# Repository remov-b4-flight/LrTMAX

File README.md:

# LrTMAX
Adobe Lightroom MIDI Developer Controller project (STM32F072Cx based)  
LrTMAX MIDI controller is formed by embedded hardware circuit board and its firmware.  
It used with [MIDI2LR](https://github.com/rsjaffe/MIDI2LR) software,  
You can control development parameters on RAW/JPEG photos.  
## Video(in brother project LrE-6)
  
detailed Video on [YouTube (LrE-6)](https://www.youtube.com/watch?v=oeDpP1sG9_Y)  
## Photo
  
LrTMAX is near to [LrE-6](https://github.com/remov-b4-flight/LrE-6)  
Information related Build,Configure & Use are exists on wiki.  
***
"Lightroom Classic" is Registerd Trademark of Adobe Corporation.

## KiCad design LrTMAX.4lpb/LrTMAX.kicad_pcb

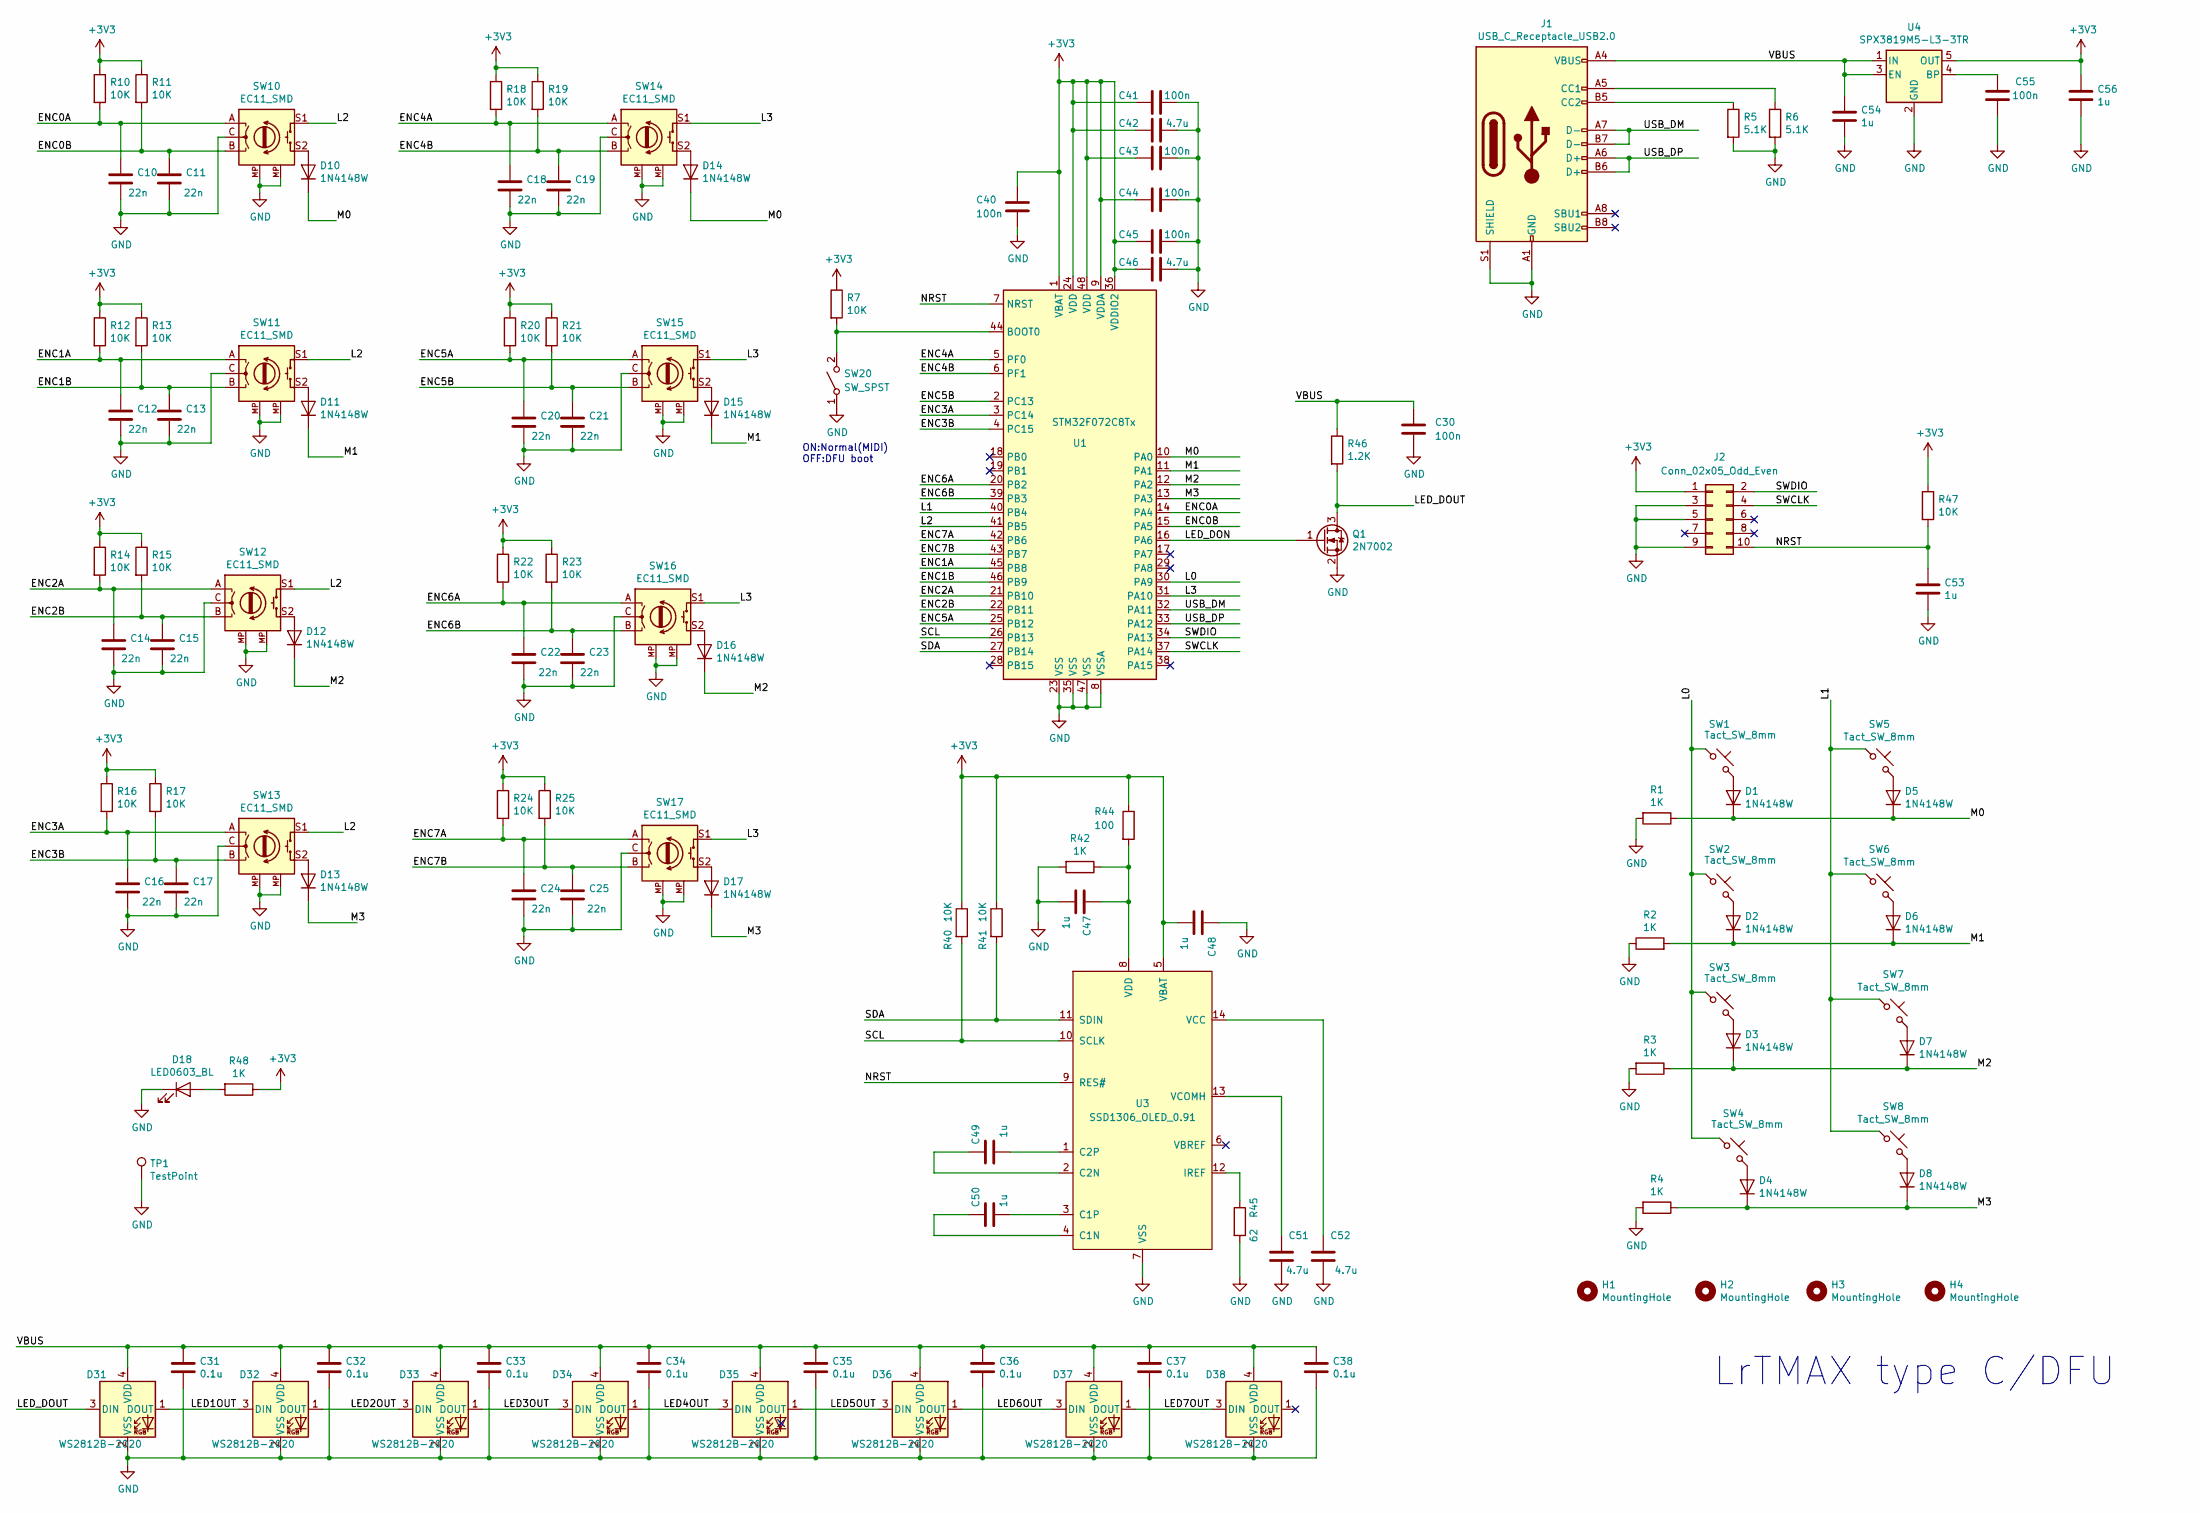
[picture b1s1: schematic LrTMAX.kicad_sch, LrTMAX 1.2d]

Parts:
C10, C11, C12, C13, C14, C15, C16, C17, C18, C19, C20, C21, C22, C23, C24, C25: 22n; C_0805_2012Metric
C30, C55: 100n; C_0805_2012Metric
C31, C32, C33, C34, C35, C36, C37, C38: 0.1u; C_0805_2012Metric
C40, C41, C43, C44, C45: 100n; C_0603_1608Metric
C42, C46, C51, C52: 4.7u; C_0805_2012Metric
C47, C48, C49, C50, C53, C54, C56: 1u; C_0805_2012Metric
D1, D2, D3, D4, D5, D6, D7, D8, D10, D11, D12, D13, D14, D15, D16, D17: 1N4148W; D_SOD-123
D18: LED0603_BL; LED_0603_1608Metric
D31, D32, D33, D34, D35, D36, D37, D38: WS2812B-2020; LED_WS2812B-2020
H1, H2, H3, H4: MountingHole; MountingHole_2.7mm_M2.5
J1: USB_C_Receptacle_USB2.0; USB_C_Receptacle_HRO_TYPE-C-31-M-12
J2: Conn_02x05_Odd_Even; PinHeader_2x05_P1.27mm_Vertical
Q1: 2N7002; SOT-23
R1, R2, R3, R4, R42, R48: 1K; R_0805_2012Metric
R5, R6: 5.1K; R_0805_2012Metric
R7, R10, R11, R12, R13, R14, R15, R16, R17, R18, R19, R20, R21, R22, R23, R24, R25, R40, R41, R47: 10K; R_0805_2012Metric
R44: 100; R_0805_2012Metric
R45: 62; R_0805_2012Metric
R46: 1.2K; R_0805_2012Metric
SW1, SW2, SW3, SW4, SW5, SW6, SW7, SW8: Tact_SW_8mm; SW_PUSH_6mm_H9.5mm
SW10, SW11, SW12, SW13, SW14, SW15, SW16, SW17: EC11_SMD; RotaryEncoder_Alps_EC11E-Switch_Vertical_H20mm
SW20: SW_SPST; SW_DIP_SPSTx01_Slide_Copal_CHS-01B_W7.62mm_P1.27mm
TP1: TestPoint; TestPoint_THTPad_D1.0mm_Drill0.5mm
U1: STM32F072C8Tx; LQFP-48_7x7mm_P0.5mm
U3: SSD1306_OLED_0.91; OLED-9.1
U4: SPX3819M5-L3-3TR; SOT-23-5

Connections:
+3V3: C40.1, C41.2, C42.2, C43.2, C44.2, C45.2, C46.2, C48.1, C56.1, J2.1, R7.1, R10.1, R11.1, R12.1, R13.1, R14.1, R15.1, R16.1, R17.1, R18.1, R19.1, R20.1, R21.1, R22.1, R23.1, R24.1, R25.1, R40.1, R41.1, R44.1, R47.1, R48.1, U1.1 (VBAT), U1.9 (VDDA), U1.24 (VDD), U1.36 (VDDIO2), U1.48 (VDD), U3.5 (VBAT), U4.5 (OUT)
/ENC0A: C10.1, R10.2, SW10.A, U1.14 (PA4)
/ENC0B: C11.1, R11.2, SW10.B, U1.15 (PA5)
/ENC1A: C12.1, R12.2, SW11.A, U1.45 (PB8)
/ENC1B: C13.1, R13.2, SW11.B, U1.46 (PB9)
/ENC2A: C14.1, R14.2, SW12.A, U1.21 (PB10)
/ENC2B: C15.1, R15.2, SW12.B, U1.22 (PB11)
/ENC3A: C16.1, R16.2, SW13.A, U1.3 (PC14)
/ENC3B: C17.1, R17.2, SW13.B, U1.4 (PC15)
/ENC4A: C18.1, R18.2, SW14.A, U1.5 (PF0)
/ENC4B: C19.1, R19.2, SW14.B, U1.6 (PF1)
/ENC5A: C20.1, R20.2, SW15.A, U1.25 (PB12)
/ENC5B: C21.1, R21.2, SW15.B, U1.2 (PC13)
/ENC6A: C22.1, R22.2, SW16.A, U1.20 (PB2)
/ENC6B: C23.1, R23.2, SW16.B, U1.39 (PB3)
/ENC7A: C24.1, R24.2, SW17.A, U1.42 (PB6)
/ENC7B: C25.1, R25.2, SW17.B, U1.43 (PB7)
/L0: SW1.1, SW2.1, SW3.1, SW4.1, U1.30 (PA9)
/L1: SW5.1, SW6.1, SW7.1, SW8.1, U1.40 (PB4)
/L2: SW10.S1, SW11.S1, SW12.S1, SW13.S1, U1.41 (PB5)
/L3: SW14.S1, SW15.S1, SW16.S1, SW17.S1, U1.31 (PA10)
/LED1OUT: D31.1 (DOUT), D32.3 (DIN)
/LED2OUT: D32.1 (DOUT), D33.3 (DIN)
/LED3OUT: D33.1 (DOUT), D34.3 (DIN)
/LED4OUT: D34.1 (DOUT), D35.3 (DIN)
/LED5OUT: D35.1 (DOUT), D36.3 (DIN)
/LED6OUT: D36.1 (DOUT), D37.3 (DIN)
/LED7OUT: D37.1 (DOUT), D38.3 (DIN)
/LED_DON: Q1.1 (G), U1.16 (PA6)
/LED_DOUT: D31.3 (DIN), Q1.3 (D), R46.2
/M0: D1.1 (K), D5.1 (K), D10.1 (K), D14.1 (K), R1.1, U1.10 (PA0)
/M1: D2.1 (K), D6.1 (K), D11.1 (K), D15.1 (K), R2.2, U1.11 (PA1)
/M2: D3.1 (K), D7.1 (K), D12.1 (K), D16.1 (K), R3.1, U1.12 (PA2)
/M3: D4.1 (K), D8.1 (K), D13.1 (K), D17.1 (K), R4.1, U1.13 (PA3)
/NRST: C53.1, J2.10, R47.2, U1.7 (NRST), U3.9 (RES#)
/SCL: R40.2, U1.26 (PB13), U3.10 (SCLK)
/SDA: R41.2, U1.27 (PB14), U3.11 (SDIN)
/SWCLK: J2.4, U1.37 (PA14)
/SWDIO: J2.2, U1.34 (PA13)
/USB_DM: J1.A7 (D-), J1.B7 (D-), U1.32 (PA11)
/USB_DP: J1.A6 (D+), J1.B6 (D+), U1.33 (PA12)
/VBUS: C30.1, C31.1, C32.1, C33.1, C34.1, C35.1, C36.1, C37.1, C38.1, C54.1, D31.4 (VDD), D32.4 (VDD), D33.4 (VDD), D34.4 (VDD), D35.4 (VDD), D36.4 (VDD), D37.4 (VDD), D38.4 (VDD), J1.A4 (VBUS), J1.A9 (VBUS), J1.B4 (VBUS), J1.B9 (VBUS), R46.1, U4.1 (IN), U4.3 (EN)
GND: C10.2, C11.2, C12.2, C13.2, C14.2, C15.2, C16.2, C17.2, C18.2, C19.2, C20.2, C21.2, C22.2, C23.2, C24.2, C25.2, C30.2, C31.2, C32.2, C33.2, C34.2, C35.2, C36.2, C37.2, C38.2, C40.2, C41.1, C42.1, C43.1, C44.1, C45.1, C46.1, C47.1, C48.2, C51.1, C52.1, C53.2, C54.2, C55.2, C56.2, D18.1 (K), D31.2 (VSS), D32.2 (VSS), D33.2 (VSS), D34.2 (VSS), D35.2 (VSS), D36.2 (VSS), D37.2 (VSS), D38.2 (VSS), J1.A1 (GND), J1.A12 (GND), J1.B1 (GND), J1.B12 (GND), J1.S1 (SHIELD), J2.3, J2.5, J2.9, Q1.2 (S), R1.2, R2.1, R3.2, R4.2, R5.2, R6.2, R42.2, R45.2, SW10.C, SW10.MP (GND), SW11.C, SW11.MP (GND), SW12.C, SW12.MP (GND), SW13.C, SW13.MP (GND), SW14.C, SW14.MP (GND), SW15.C, SW15.MP (GND), SW16.C, SW16.MP (GND), SW17.C, SW17.MP (GND), SW20.1 (A), TP1.1, U1.8 (VSSA), U1.23 (VSS), U1.35 (VSS), U1.47 (VSS), U3.7 (VSS), U4.2 (GND)
unnamed: C47.2, R42.1, R44.2, U3.8 (VDD)
unnamed: C49.1, U3.2 (C2N)
unnamed: C49.2, U3.1 (C2P)
unnamed: C50.1, U3.4 (C1N)
unnamed: C50.2, U3.3 (C1P)
unnamed: C51.2, U3.13 (VCOMH)
unnamed: C52.2, U3.14 (VCC)
unnamed: C55.1, U4.4 (BP)
unnamed: D1.2 (A), SW1.2
unnamed: D2.2 (A), SW2.2
unnamed: D3.2 (A), SW3.2
unnamed: D4.2 (A), SW4.2
unnamed: D5.2 (A), SW5.2
unnamed: D6.2 (A), SW6.2
unnamed: D7.2 (A), SW7.2
unnamed: D8.2 (A), SW8.2
unnamed: D10.2 (A), SW10.S2
unnamed: D11.2 (A), SW11.S2
unnamed: D12.2 (A), SW12.S2
unnamed: D13.2 (A), SW13.S2
unnamed: D14.2 (A), SW14.S2
unnamed: D15.2 (A), SW15.S2
unnamed: D16.2 (A), SW16.S2
unnamed: D17.2 (A), SW17.S2
unnamed: D18.2 (A), R48.2
unnamed: J1.A5 (CC1), R6.1
unnamed: J1.B5 (CC2), R5.1
unnamed: R7.2, SW20.2 (B), U1.44 (BOOT0)
unnamed: R45.1, U3.12 (IREF)

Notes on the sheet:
LrTMAX type C/DFU
ON:Normal(MIDI) OFF:DFU boot

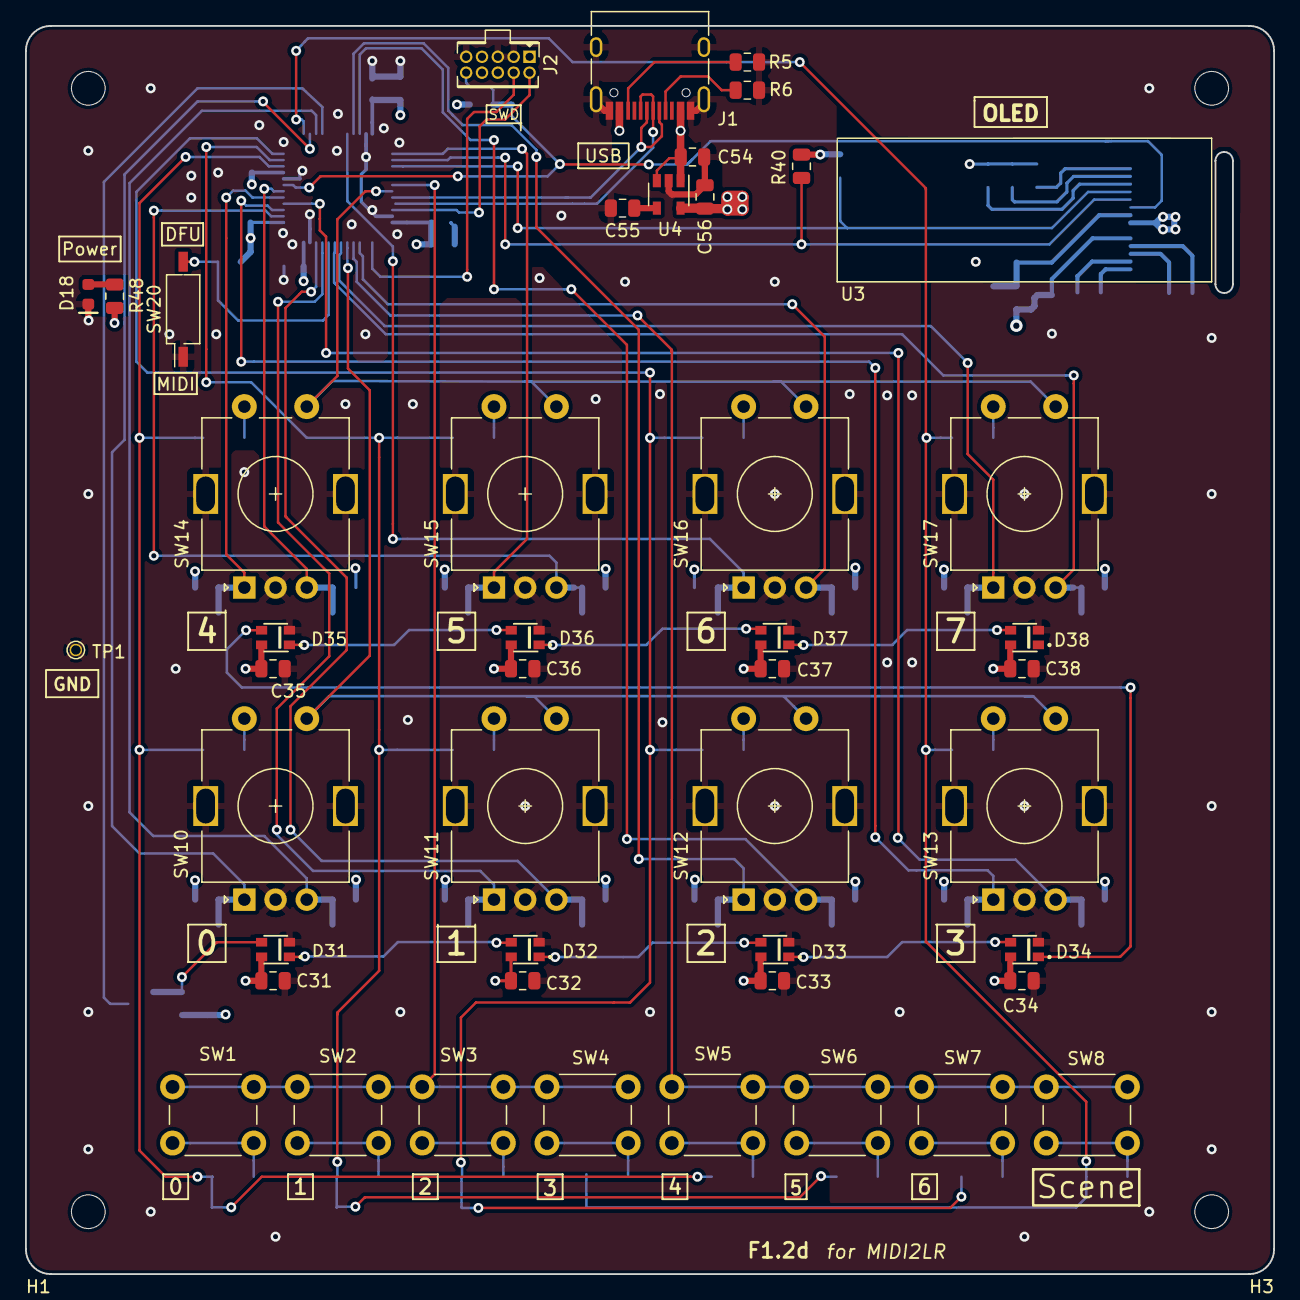
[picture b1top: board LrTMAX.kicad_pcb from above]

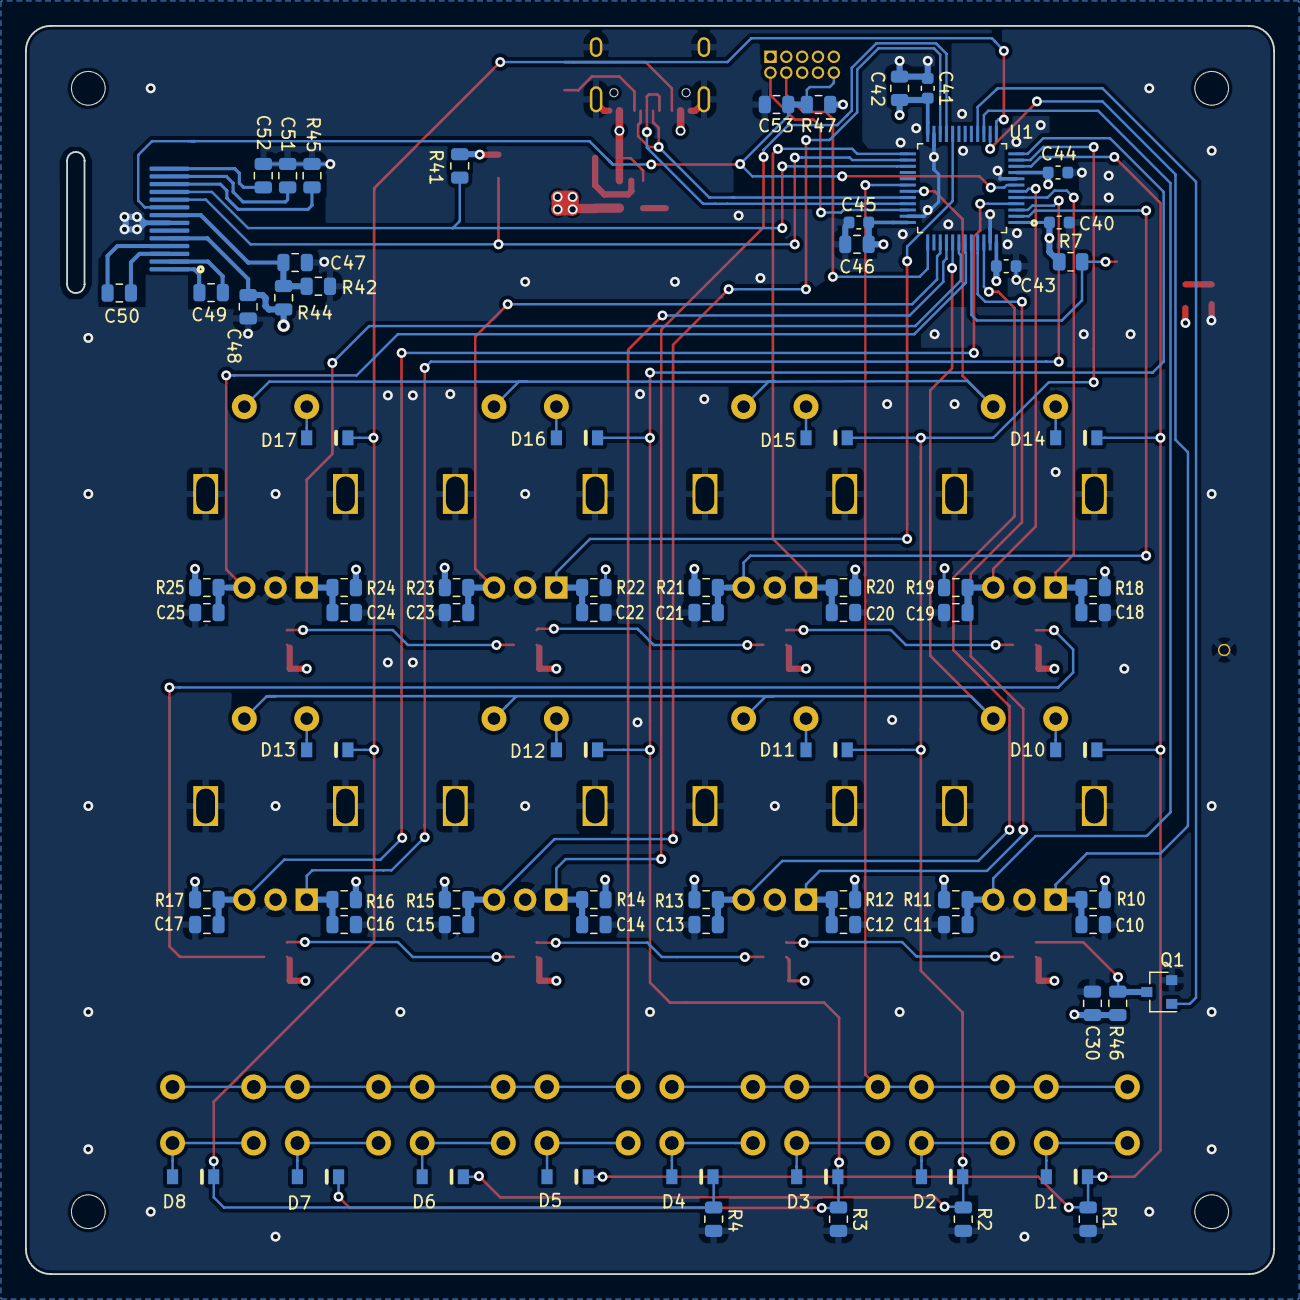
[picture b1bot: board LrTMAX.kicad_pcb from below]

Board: 4 copper layers, 100.0 x 100.0 mm, 126 parts (76 on the bottom side), 72 nets.

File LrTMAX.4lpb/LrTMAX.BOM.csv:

Item,Qty,Reference(s),Value,LibPart,Footprint,Purchase URL
1,3,"C43, C44, C45",100n,LrE-6-rescue:C-Device,Capacitor_SMD:C_0603_1608Metric,
2,12,"C30, C31, C32, C33, C34, C35, C36, C37, C38, C40, C41, C55",100n,LrE-6-rescue:C-Device,Capacitor_SMD:C_0805_2012Metric,
3,4,"C42, C46, C51, C52",4.7u,LrE-6-rescue:C-Device,Capacitor_SMD:C_0805_2012Metric,
4,7,"C47, C48, C49, C50, C53, C54, C56",1u,LrE-6-rescue:C-Device,Capacitor_SMD:C_0805_2012Metric,
5,16,"D1, D2, D3, D4, D5, D6, D7, D8, D10, D11, D12, D13, D14, D15, D16, D17",1N4148W,LrE-6-rescue:1N4148W-Diode,LrE-6:D_SOD-123,https://www.aliexpress.com/item/32829336693.html
6,1,D18,LED0603_BL,LrE-6-rescue:LED-Device,LED_SMD:LED_0603_1608Metric,https://www.aliexpress.com/item/32888575577.html
7,8,"D31, D32, D33, D34, D35, D36, D37, D38",WS2812B-2020,LrE-6:WS2812B-2020,LrE-6:LED_WS2812B-2020,https://www.aliexpress.com/item/32995819792.html
8,4,"H1, H2, H3, H4",MountingHole,LrE-6-rescue:MountingHole-Mechanical,MountingHole:MountingHole_3.2mm_M3,
9,1,J1,USB_C_Receptacle_USB2.0,LrE-6:USB_C_Receptacle_USB2.0,Connector_USB:USB_C_Receptacle_HRO_TYPE-C-31-M-12,https://ja.aliexpress.com/item/1005002157048896.html
10,1,J2,SM06B-SRSS-TB,LrE-6-rescue:Conn_01x06-Connector_Generic,Connector_JST:JST_SH_SM06B-SRSS-TB_1x06-1MP_P1.00mm_Horizontal,https://www.aliexpress.com/item/32831122807.html
11,1,Q1,2N7002,LrE-6-rescue:2N7002-Transistor_FET,Package_TO_SOT_SMD:SOT-23,https://www.aliexpress.com/item/32843479156.html
12,5,"R1, R2, R3, R4, R48",1K,LrE-6-rescue:R-Device,Resistor_SMD:R_0805_2012Metric,
13,20,"R7,R10, R11, R12, R13, R14, R15, R16, R17, R18, R19, R20, R21, R22, R23, R24, R25, R40, R41, R47",10K,LrE-6-rescue:R-Device,Resistor_SMD:R_0805_2012Metric,
14,1,R42,1K,LrE-6-rescue:R-Device,Resistor_SMD:R_0805_2012Metric,
15,1,R44,100,LrE-6-rescue:R-Device,Resistor_SMD:R_0805_2012Metric,
16,1,R45,62,LrE-6-rescue:R-Device,Resistor_SMD:R_0805_2012Metric,
17,1,R46,1.2K,LrE-6-rescue:R-Device,Resistor_SMD:R_0805_2012Metric,
18,8,"SW1, SW2, SW3, SW4, SW5, SW6, SW7, SW8",Tact_SW_8mm,LrE-6-rescue:SW_Push_45deg-Switch,Button_Switch_THT:SW_PUSH_6mm_H9.5mm,https://www.aliexpress.com/item/1058764733.html
19,8,"SW10, SW11, SW12, SW13, SW14, SW15, SW16, SW17",EC11_SMD,LrE-6-rescue:Rotary_Encoder_Switch-Device,Rotary_Encoder:RotaryEncoder_Alps_EC11E-Switch_Vertical_H20mm,https://www.aliexpress.com/item/33051669996.html
20,1,U1,STM32F072C8Tx,LrE-6-rescue:STM32F072C8Tx-MCU_ST_STM32F0,Package_QFP:LQFP-48_7x7mm_P0.5mm,https://www.aliexpress.com/item/1005001604196690.html
21,1,U3,SSD1306_OLED_0.91,LrE-6:OLED-0.91,LrE-6:OLED-9.1,https://www.aliexpress.com/item/32787123531.html
22,1,U4,SPX3819M5-L3-3TR,LrE-6-rescue:LDK130-08_SOT23_SOT353-Regulator_Linear,Package_TO_SOT_SMD:SOT-23-5,https://www.aliexpress.com/item/32703161484.html
23,16,"C10, C11, C12, C13, C14, C15, C16, C17, C18, C19, C20, C21, C22, C23, C24, C25,",22n,LrE-6-rescue:C-Device,Capacitor_SMD:C_0805_2012Metric,
24,1,R8,0,LrE-6-rescue:R-Device,Resistor_SMD:R_0805_2012Metric,

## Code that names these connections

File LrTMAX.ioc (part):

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Mcu.Name=STM32F072C(8-B)Tx
Mcu.Package=LQFP48
Mcu.UserName=STM32F072C8Tx
PA0.GPIOParameters=GPIO_Label
PA0.GPIO_Label=M0
PA0.Signal=GPIO_Input
PA1.GPIOParameters=GPIO_Label
PA1.GPIO_Label=M1
PA1.Signal=GPIO_Input
PA10.GPIOParameters=GPIO_Label
PA10.GPIO_Label=L3
PA10.Signal=GPIO_Output
PA11.GPIOParameters=GPIO_Label
PA11.GPIO_Label=USB_DM
PA11.Mode=Device
PA11.Signal=USB_DM
PA12.GPIOParameters=GPIO_Label
PA12.GPIO_Label=USB_DP
PA12.Mode=Device
PA12.Signal=USB_DP
PA13.GPIOParameters=GPIO_Label
PA13.GPIO_Label=SWDIO
PA13.Mode=Serial_Wire
PA13.Signal=SYS_SWDIO
PA14.GPIOParameters=GPIO_Label
PA14.GPIO_Label=SWCLK
PA14.Mode=Serial_Wire
PA14.Signal=SYS_SWCLK
PA2.GPIOParameters=GPIO_Label
PA2.GPIO_Label=M2
PA2.Signal=GPIO_Input
PA3.GPIOParameters=GPIO_Label
PA3.GPIO_Label=M3
PA3.Signal=GPIO_Input
PA4.GPIOParameters=GPIO_Label
PA4.GPIO_Label=ENC0A
PA4.Signal=GPIO_Input
PA5.GPIOParameters=GPIO_Label
PA5.GPIO_Label=ENC0B
PA5.Signal=GPIO_Input
PA6.GPIOParameters=GPIO_Label
PA6.GPIO_Label=LED_DON
PA6.Signal=S_TIM3_CH1
PA9.GPIOParameters=GPIO_Label
PA9.GPIO_Label=L0
PA9.Signal=GPIO_Output
PB10.GPIOParameters=GPIO_Label
PB10.GPIO_Label=ENC2A
PB10.Signal=GPIO_Input
PB11.GPIOParameters=GPIO_Label
PB11.GPIO_Label=ENC2B
PB11.Signal=GPIO_Input
PB12.GPIOParameters=GPIO_Label
PB12.GPIO_Label=ENC5A
PB12.Signal=GPIO_Input
PB13.GPIOParameters=GPIO_Label,GPIO_Pu
PB13.GPIO_Label=SCL
PB13.GPIO_Pu=GPIO_PULLUP
PB13.Mode=I2C
PB13.Signal=I2C2_SCL
PB14.GPIOParameters=GPIO_Label,GPIO_Pu
PB14.GPIO_Label=SDA
PB14.GPIO_Pu=GPIO_PULLUP
PB14.Mode=I2C
PB14.Signal=I2C2_SDA
PB2.GPIOParameters=GPIO_Label
PB2.GPIO_Label=ENC6A
PB2.Signal=GPIO_Input
PB3.GPIOParameters=GPIO_Label
PB3.GPIO_Label=ENC6B
PB3.Signal=GPIO_Input
PB4.GPIOParameters=GPIO_Label
PB4.GPIO_Label=L1
PB4.Signal=GPIO_Output
PB5.GPIOParameters=GPIO_Label
PB5.GPIO_Label=L2
PB5.Signal=GPIO_Output
PB6.GPIOParameters=GPIO_Label
PB6.GPIO_Label=ENC7A
PB6.Signal=GPIO_Input
PB7.GPIOParameters=GPIO_Label
PB7.GPIO_Label=ENC7B
PB7.Signal=GPIO_Input
PB8.GPIOParameters=GPIO_Label
PB8.GPIO_Label=ENC1A
PB8.Signal=GPIO_Input
PB9.GPIOParameters=GPIO_Label
PB9.GPIO_Label=ENC1B
PB9.Signal=GPIO_Input
PC13.GPIOParameters=GPIO_Label
PC13.GPIO_Label=ENC5B
PC13.Signal=GPIO_Input
PC14-OSC32_IN.GPIOParameters=GPIO_Label
PC14-OSC32_IN.GPIO_Label=ENC3A
PC14-OSC32_IN.Signal=GPIO_Input
PC15-OSC32_OUT.GPIOParameters=GPIO_Label
PC15-OSC32_OUT.GPIO_Label=ENC3B
PC15-OSC32_OUT.Signal=GPIO_Input
PF0-OSC_IN.GPIOParameters=GPIO_Label
PF0-OSC_IN.GPIO_Label=ENC4A
PF0-OSC_IN.Signal=GPIO_Input
PF1-OSC_OUT.GPIOParameters=GPIO_Label
PF1-OSC_OUT.GPIO_Label=ENC4B
PF1-OSC_OUT.Signal=GPIO_Input
RCC.SYSCLKFreq_VALUE=48000000
RCC.SYSCLKSource=RCC_SYSCLKSOURCE_HSI48
board=custom

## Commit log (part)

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2021-07-20 0.47-10
2021-07-22 0.47-11
    some refactoring,fixes, workarounds.
2021-07-23 0.47-12
    LED fixing intermidiate.
2021-07-23 0.48
    Clean up & Add comment.
2021-07-23 0.48-1
    Fix for I2C on Release build not work.
2021-07-24 0.48-3
    Fix Comments
2021-08-15 0.48-4
    Adjust LED pink color.
2021-09-09 0.48-6
    Fix incorrect descriptor
2021-09-18 0.49-pre
2021-10-02 0.49-pre3m
2021-10-07 0.49-pre6m
    move to F0_11.3
2021-10-14 0.49c
    USB conn. changed to typeC
2021-10-15 0.49c-1
    Add SLA0044 licence.
2021-10-16 0.49c-2
    ADC stopped.
2021-10-21 0.49c-4
    Fix issue #1 (Remove HAL_TIM_Base_Init(&htim14) from Delay_us() )
2021-10-22 0.51
    version feeding (avoid LrE-6 conflict)
2021-10-23 0.53-3
    Eliminate un-needed.
2021-10-25 0.51-3
    Change key scan rates to 4*8ms=32ms
2021-10-25 0.51-5
    remove un-needed symbols
2021-10-25 0.51-6
    remove isKeyReleaseSent related func.
2021-10-26 0.51-9
    Eliminate isKeyReleaseSent
2021-10-27 0.51-9
    Move Delay_us() to led.c (related with #1)
2021-10-27 0.51-11
    issue #3 adopted.
2021-10-28 0.51-12
    Change Licence to "3-clause BSD".
    Create 'bitmapmaker.xls' OLED bitmap generator.
    Fix version display in Debug build.
2021-10-28 Create LICENCE
    Change to 3-Clause BSD License.
2021-10-28 0.52
    Version feed.
2021-10-29 0.52-2
    Fix ssd1306 rendering.
2021-10-29 0.52-4
    Fix comments & and remove unused function declaration in main.h .
2021-10-30 0.53-pre
    offline mode defunctioned
2021-11-01 0.53
    Use TIM7 for OLED Timer.
    Fix issue #2.
    Refactoring.
2021-11-02 0.53-1
    Fix long MsgTimer interval
    Moved LED Timer TIM1 to TIM6
    Fix #5 (suspend TIM1 start until USB link up)
2021-11-02 0.53-3
    Fix issue #4 by redesign connect bitmap,non-overlap with version
    display.
2021-11-02 0.53-4
    Save design data
2021-11-09 0.54-1
    Fix batting LED lighting on USB connect.
2021-11-11 0.54-2
    Activate TIM15 for cancel chatter from ENCx
2021-11-13 0.55-pre2
2021-11-14 0.55-pre3
    Fix de-chatter cap. values to 22nF -> 100nF
2021-11-14 0.55
    Optimize All ENCx ISR for faster exit.
2021-11-15 0.55-1
    Stop using TIM15
2021-11-17 Update gitattributes & gitignore
2021-11-23 0.55-3
    Adjust sleep.
2021-11-27 0.55-4
    Re-enables sleep.
2021-12-07 0.55-6
    Remove Unsed MIDI Routines.
2021-12-07 0.55-7
    Change timing as 'USB Connected'
2021-12-11 0.55-9
2021-12-15 0.55-10
    Function assign modification Scene0 A6,A7 as quick development.
    Revert back 'connect indication' by setup packet id received.
2021-12-17 0.55-12
    remove HID dependency.
2021-12-17 0.55-12
    exclude un-needed.
2021-12-17 0.55-15
    Update /MIDI2LR/LrTMAX.xml
2021-12-18 0.56
    Version feeding.
2021-12-31 0.56-2
    add 'cc chanel offset'. experimenal
2021-12-31 0.56-3
    Fix CC channels per scene for 10 -> 8
2021-12-31 0.56-4
    Fix Key Assignments & LED colors.
2022-01-04 0.57-1
    Fix CC channel offset 40 -> 64
    Now LrTMAX act as keyboard that has no velocity support.
2022-01-05 0.57-2
    remove un-needed.
2022-01-08 0.57-4
    invalidate MIDI_DataRx() for fix MIDI_CC_Value() destruction by
    invalid index.
2022-01-10 0.57-5
2022-01-10 0.57-7
2022-01-10 0.57-8
    Copy Synthstation25 audio class descriptors.
2022-01-11 0.58-pre2
    Reflect recived CC comand value to MIDI_CC_VALUE[] array.
2022-01-12 0.58-pre3
2022-01-12 0.58
    Fixed issue #8 totally.
2022-01-19 0.58-1
2022-01-28 0.58-2
2022-02-01 0.58-3
    modify case
2022-02-12 0.58-4
    some refactoring.
2022-02-23 0.58-6
    fixing #10 issue, MIDI_DataRx() rewrited.
2022-02-23 0.58-7
    EmulateMIDI modifies to use MIDI_EVENT struct.
2022-02-24 0.59-1
2022-02-26 0.59-4
    Split definitions for LrCommon.h
2022-02-26 0.59-6
2022-02-28 0.59-8
2022-03-04 0.59-10
    refine key_define.c comments.
    fix variable scope.
2022-03-04 0.59-11
    move LED_SetScene() to led.c
2022-03-04 0.95-13
    adjust build optimize.
2022-03-04 0.59-14
    adjust build optimization again.
2022-03-08 0.59-16
    Case-noscrew added.
2022-05-19 0.59-17
2022-05-19 0.59-18
    experimental fix for #11 issue.
2022-05-24 0.59-20
    Reversed 0.59-19
2022-06-06 0.59-21
    Fix indents.
2022-07-13 0.60-pre0
    Enable TIM15 for de-chatter.
2022-07-14 0.60-pre1
2022-07-15 0.60-pre3
    TIM15 based de-chattering.
    Fix NeoPixel RESET wait.
    Change TIM14 as 'one pulse mode'
2022-07-16 0.60-pre4
    Refine stm32f0_it.c structure
    Rename macro symbol name for timers
2022-07-16 0.60-pre6
    unify build settings between Release and Debug.
2022-07-18 0.60-pre7
    Modify dechatter period 1000ms to 1500ms
2022-07-19 0.60
    version feed.
2022-07-22 0.60-10
    Change USB-MIDI Initialize timing (to eazy MX code regeneration)
2022-09-24 Mechanical de-chatter first implementation
2022-09-25 0.61-1
    modify LRTMAX.ioc for match with source
2022-09-25 0.61-2
    modify LrTMAX.ioc again
2022-09-28 0.61-5
    Update LrTMAX.ioc
2022-10-19 0.61-7
    Adjust TIM_PERIOD_DCHAT to 150ms
2022-12-21 0.61-10
    only key assignment.
2023-01-17 0.61-4
    Unify MX_USB_DEVICE_INIT and MX_USB_MIDI_INIT.
2023-01-18 0.61-11
    Fix for code genaration again.
2023-01-18 0.61-12
    3rd fix for code regenerate.
2023-01-19 0.62-pre0
2023-01-21 0.62-pre1
    fix Jump2SystemMemory()
2023-01-28 0.62-00
    add kicad 6.0 pattern to LrTMAX.l4pb/gitignore
2023-01-30 0.62-00.12cc
    Modify "BOOT0" connection on PCB as "1.2cc"
2023-02-04 0.62-1
    Add 'Reset LrTMAX' functionality with key combination.
2023-02-22 0.62-2a
    Add LrE-6 animation gif
2023-02-22 0.62-2b
    modify README.md
2023-03-11 0.62-4
    Change MIDI note velocity to 127 from 64.
2023-03-12 0.62-6
    Version skipping same as 0.62-3
2023-03-13 0.62-11
    Again Note velocity set to 127 from 64.
2023-03-16 0.62-12
    Initialze Matrix when USB connect and Stop when disconnect.
2023-03-17 0.63
    create matrix start/stop as function.
2023-03-19 0.63-1
    Restore matrix initialize for DFU boot.
2023-03-23 Added DFU DIP Switch.
2023-03-26 Refine pattern.
2023-03-26 Fix BOM .csv file.
2023-04-04 modify PCB BOM for JLCPCB Asslembly order(just a test)
2023-04-15 0.63-2
    Just alignment fix after LrTMAX_l4pb_1.2d is marged.
2023-05-09 added splitted submodules
2023-05-13 Split out Documents
2023-05-13 move MIDI2LR/LrTMAX.xml to LrTMAX.documents
2023-05-13 Changed submodule reference
2023-05-21 0.63-3-ccrotary
    prepare for ccrotary
2023-05-22 0.63-4
    cc-rotary omit keyconfig .type
2023-05-22 modify LrTMAX.4lpb
2023-05-22 Modify LrTMAX.config
2023-05-22 LrTMAX.4lpb change
2023-05-23 0.64-pre2
    edit key_define.c
2023-05-29 0.64-pre5
2023-06-04 0.64-pre6
    Update documents
2023-06-04 0.64-pre7
    Modified USB config descriptors that based on KORG nanoKONTROL2
2023-06-05 0.65-pre1
    Version Feeding
2023-06-05 0.64
    Version Feeding.
2023-06-05 0.65-pre3
    copied EP setting from nanoKONTROL2
2023-06-06 0.65-pre4
    Restored USB Config descrioptor for 'REMOTE_WAKEUP' bit.
2023-06-20 0.65-1
    Modify key_define.c to use local adjustment.
2023-06-26 0.65-2
    Split EmilateMIDI() function.
2023-06-27 0.65-4
    more Accurate nonoKontrol2 emulation
2023-06-27 0.65-5
    CC_CH_OFFSET (CC channel offset) set 0
2023-06-28 0.65-7
    fix key_define.c
2023-06-29 0.65-8
2023-06-30 0.65-20
2023-07-01 0.65-21
    Cleaned up un-needed codes.
2023-07-03 0.65-22
    Fix MIDI_DataRx() to store for MIDI_CC_VALUE[] collectly.
2023-07-03 0.65-24
    fix key_define.c
2023-07-04 0.66-pre0
    Omited Key assign string on OLED screen.
2023-07-05 EmulateMIDI.c を更新
2023-07-05 LrCommon.h を更新
2023-07-05 0.66-pre2
    Adjust encoder's Note numbers same as CC channel numbers.
2023-07-05 0.66-pre3
    fix Note number for encoder push.
2023-07-06 0.66-pre5
    refactoring
2023-07-06 0.66-pre6
    refactoring.
2023-07-06 0.66-pre8
    prof_define.c
2023-07-06 0.66-pre9
    LrTMAX.config
2023-07-15 follow LrTMAX.4lpb new Release
2023-07-17 0.66-1
    Add queueing for recrived midi messages
2023-07-17 0.66-2
    add queue_isempty()
2023-07-18 0.66-4
    follow the warnings.
2023-07-18 0.66-5
2023-07-20 0.66-7
2023-07-22 0.66-8
    LrTMAX.4lpb board order
2023-07-24 0.67-1
    Move MIDI_CC_Inc/Dec EmulateMIDI() from ISR's
2023-07-24 0.67-2
    fix CW/CCW for Inc/Dec.
2023-07-26 0.67-a
    modify optimize to O2
2023-07-26 0.67-2b
2023-07-28 0.67-5
2023-07-28 0.67-6
    fix build environments
2023-07-29 0.67-7
    Fixed encoder ISRs to chatter does not make changes any internal states.
2023-07-29 0.67-9
2023-07-29 0.67-10
2023-07-30 0.67-12
    some refactoring
2023-07-31 0.67-13
    refactoring
2023-08-01 0.68-pre1
2023-08-01 0.68-pre2
    After generate codes by STM32CubeMX in STM32CubeIDE
2023-08-01 0.68-pre4
2023-08-07 0.67-14
    add enc_prev[] initialization by pin conditions.
2023-08-10 0.68-pre6
    encoder detection
2023-08-11 0.67-15stm32f0xx_it.c
2023-08-11 0.67-17
    Moved Encoder Initialization as ENC_Init() on stm32f0xx_it.c
2023-08-11 0.68-pre8
    OK with Encoder move to MIDI message send.
2023-08-11 0.68-pre9
    Fix for duplicated MIDI messages from encoder.
2023-08-11 0.68-pre11
    Fix build errors
2023-08-12 0.68-pre12
    fix only typos.
2023-08-12 0.68-pre14
    Fix optimization to -O2 from -O3
2023-08-12 0.68
    add doxygen comments.
2023-08-13 0.68-2
    Add comment only
2023-08-14 0.68-3
2023-08-19 0.68-5
    queue.c & .h converted to ring buffer.
2023-08-23 0.68-6
    buffer adjustment.
2023-08-25 0.68-8
    Fix HAL_PCDEx_PMAConfig()
2023-08-25 0.69-pre0
    Modify HAL_PCDEx_PMAConfig() parameters to
    match with LrTMAX USB endpoints.
2023-08-25 0.69-pre2
    Add doxygen comments
2023-08-25 0.69-pre3
    Add comments.
2023-08-25 0.69
    Add comments and version feed.
2023-08-28 0.59-2
    fix doxygen comments only
2023-08-28 0.69-4
2023-08-29 0.67-8
    Add comments
2023-09-02 0.69-9
    Modify to Pick initial encoder condition on USB connect.
2023-09-04 0.69-11
    Add doxygen comments.
2023-09-04 0.69-11
    Add comments.
2023-09-06 0.69-13
    modify LED pattern
2023-09-08 0.69-14
    Add LED color
2023-09-11 0.69-16
    Add filess for STM32 VSCode extention.
2023-09-11 0.69-17
    Add #define symbol
2023-09-22 0.69-19
    Fix comments.
2023-10-20 0.69-20
    Modiffy opr_define.c assignment.
2024-01-11 0.69-21
    Modify to use HAL function in LED DMA initialize.
2024-02-14 0.70-pre1
2024-03-13 0.70-pre2
    Change LED initialize order to top.
2024-03-18 0.70-1
    Comment only(enum/structure elements), .gitignore
2024-03-18 remove unneeded
2024-06-15 0.70-2
    moved STM32 firmware to F0_V1.11.5
2024-06-22 reflect submodule modify
2024-07-14 0.71
    Scene timer added.
    If no touch with swith/rotator 1 hour, Scene back to SCENE0.
2024-07-14 0.71-1
    Fix pressing Scene0 button on software.
2024-07-18 0.71-3
    Make build option to not use "SCENE TIMEOUT"
2024-08-20 Update usbd_desc.c part2
2024-08-20 Update usbd_desc.c part3
2024-08-20 0.71-10
    Marge upstream changes.
2024-08-21 0.71-11
    set USE_HAL_PCD_REGISTER_CALLBACKS to 1 and define
    own callback functions with SetupStage and Disconnect.
2024-08-22 0.71-13
    Modify include order.
2024-08-22 0.71-14
    Change linker script with genarated by newer STM32CubeIDE.
2024-08-23 0.71-16
    Fix for reduce regenatete work.(part2)
2024-08-24 0.71-17
    follow STM32CubeIDE code generation.
2024-08-25 0.71
    Fix DFU can't launch by key combination at powering.
2024-08-25 0.71-20
    Fix comment only.
2024-08-28 0.72-pre0
    Just only version feeding.
2024-09-06 0.72-pre2
    Add func. declearation of Jump2SystemMemory()
2024-09-07 0.72-pre2b
    Fix for comments.
2024-09-15 0.72-pre3
    Rollback to USE_HAL_PCD_REGISTER_CALLBACKS = 0
2024-10-21 0.72-1
2024-10-21 0.72-2
    just defice constant for readablity.
2024-10-22 0.72-3
2024-10-22 0.72-5
2024-10-22 0.72-6
    Fix typos.
2024-10-26 0.72-8
    Fix unintentional D31 flash by any encoder push.
2024-11-02 0.72-9
    Fix LEDs does not flash.
2025-04-07 0.72-11
    Comment only.
2025-04-19 0.72-12
    Extend SSD1306 power-up time wait.
2025-10-19 0.72-14
    Version feed for before make branch
2025-10-25 0.73-pre
    change rotary encoder scan rate 1666 -> 2000us
2025-11-15 0.73
    encoder chatter reduction by timer
    operation detected within 50ms from prev. MIDI send. that is skipped.
2025-11-15 0.73-1
    adjust DECHATTER_TO shorter.
2025-11-24 0.74-pre
2025-11-24 0.74-pre2
    allow descend limits.
2025-11-24 0.74-pre3
    some tweaking.
2025-12-06 set debug optimize to Og from O0
2025-12-06 0.74-1
    some refactoring.
2026-01-18 0.74-3
    Comment only.
2026-03-23 0.74-4
    Add only comment on EmulateMIDI.c
2026-04-02 0.74-5
    Edit README.md
